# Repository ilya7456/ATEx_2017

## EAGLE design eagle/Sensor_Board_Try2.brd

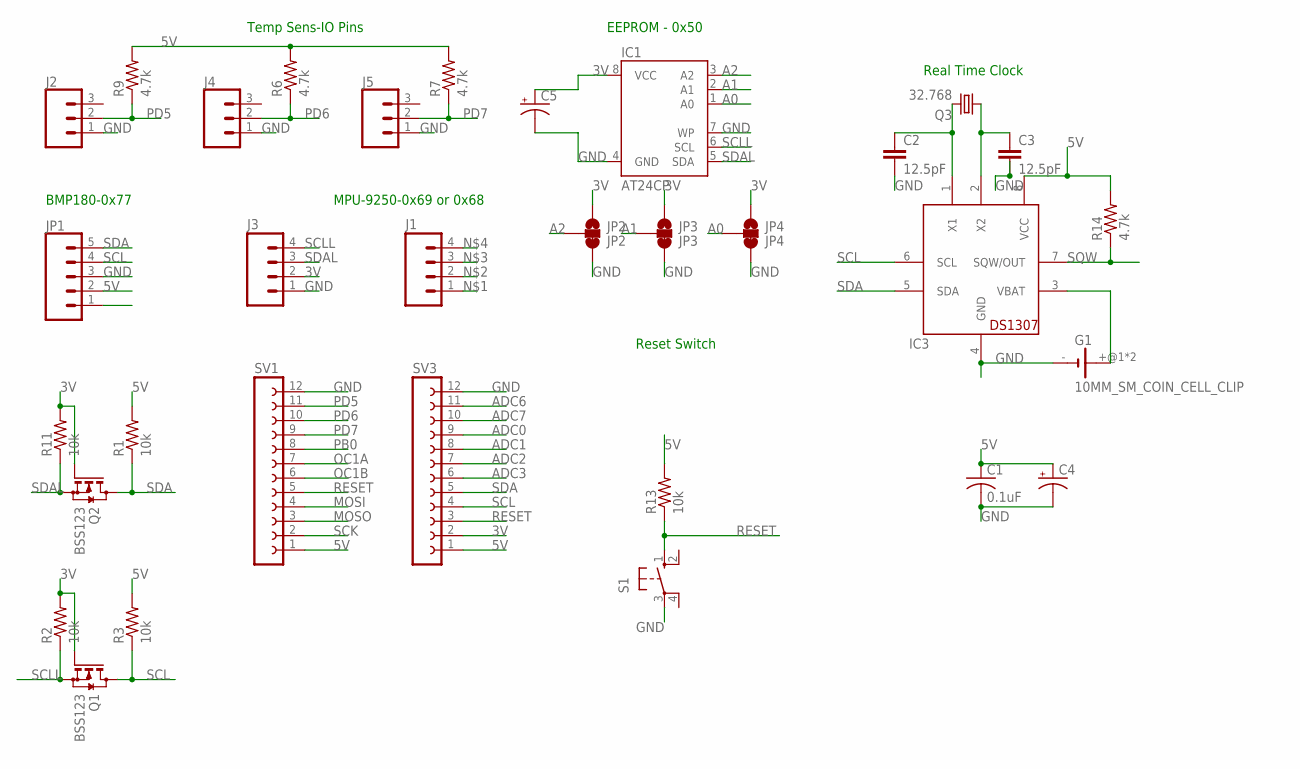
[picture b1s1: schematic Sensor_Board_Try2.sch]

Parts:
C1: 0.1uF; C025-025X050
C2, C3: 12.5pF; C0805
C4, C5: CPOL-USE2-4; E2-4
G1: 10MM_SM_COIN_CELL_CLIP
IC1: AT24CP; DIL08
IC3: DS1307; DIL08
J1, J3: M04PTH; 1X04
J2, J4, J5: CONN_03; 1X03
JP1: CONN_05; 1X05
JP2: JP2; SMT-JUMPER_3_1-NC_TRACE_SILK
JP3: JP3; SMT-JUMPER_3_1-NC_TRACE_SILK
JP4: JP4; SMT-JUMPER_3_1-NC_TRACE_SILK
Q1, Q2: BSS123; SOT23
Q3: 32.768; TC38H
R1, R2, R3, R11, R13: 10k; M0805
R6, R7, R9, R14: 4.7k; M0805
S1: 10-XX; B3F-10XX
SV1, SV3: FE12-1; FE12

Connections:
3V: C5.+, IC1.8 (VCC), J3.2, JP2.1, JP3.1, JP4.1, Q1.1 (G), Q2.1 (G), R2.2, R11.2, SV3.2
5V: C1.1, C4.+, IC3.8 (VCC), JP1.2, R1.2, R3.2, R6.2, R7.2, R9.2, R13.2, R14.2, SV1.1, SV3.1
A0: IC1.1 (A0), JP4.2
A1: IC1.2 (A1), JP3.2
A2: IC1.3 (A2), JP2.2
ADC0: SV3.9
ADC1: SV3.8
ADC2: SV3.7
ADC3: SV3.6
ADC6: SV3.11
ADC7: SV3.10
GND: C1.2, C2.2, C3.2, C4.-, C5.-, G1.-, IC1.4 (GND), IC1.7 (WP), IC3.4 (GND), J2.1, J3.1, J4.1, J5.1, JP1.3, JP2.3, JP3.3, JP4.3, S1.3, SV1.12, SV3.12
MOSI: SV1.4
MOSO: SV1.3
unnamed: C2.1, IC3.1 (X1), Q3.2
unnamed: C3.1, IC3.2 (X2), Q3.1
OC1A: SV1.7
OC1B: SV1.6
PB0: SV1.8
PD5: J2.2, R9.1, SV1.11
PD6: J4.2, R6.1, SV1.10
PD7: J5.2, R7.1, SV1.9
RESET: R13.1, S1.1 (S), SV1.5, SV3.3
SCK: SV1.2
SCL: IC3.6 (SCL), JP1.4, Q1.3 (D), R3.1, SV3.4
SCLL: IC1.6 (SCL), J3.4, Q1.2 (S), R2.1
SDA: IC3.5 (SDA), JP1.5, Q2.3 (D), R1.1, SV3.5
SDAL: IC1.5 (SDA), J3.3, Q2.2 (S), R11.1
SQW: IC3.7 (SQW/OUT), R14.1
VBAT: G1.+@1 (+), G1.+@2 (+), IC3.3 (VBAT)

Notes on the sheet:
BMP180-0x77
MPU-9250-0x69 or 0x68
Temp Sens-IO Pins
EEPROM - 0x50
Reset Switch
Real Time Clock

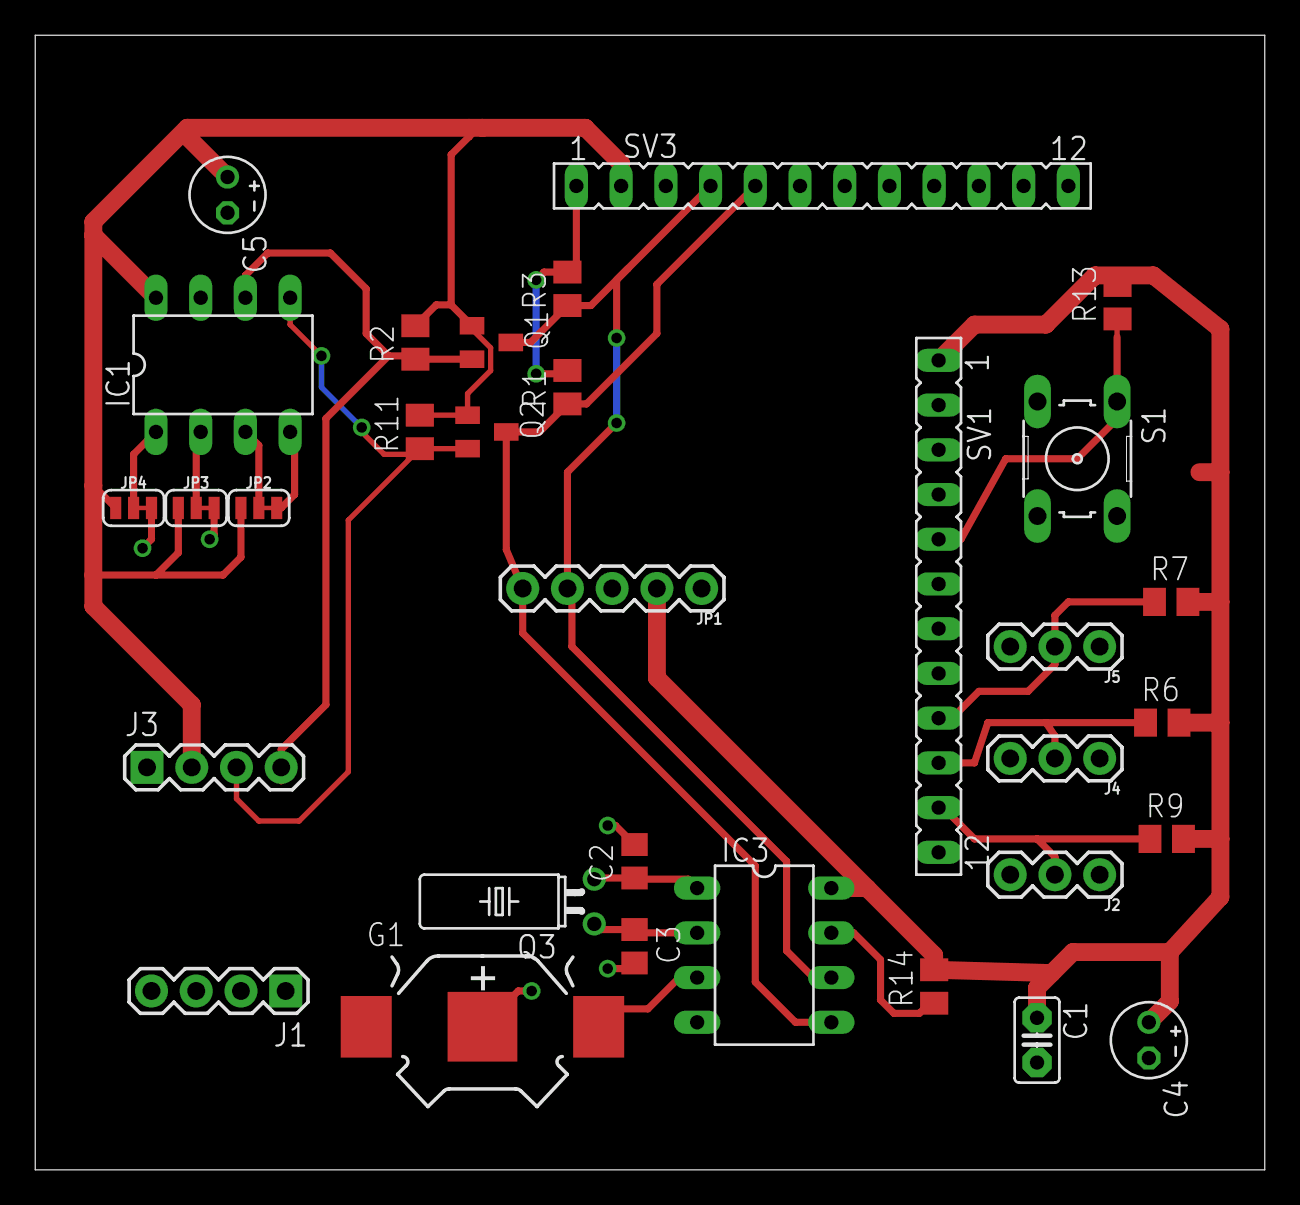
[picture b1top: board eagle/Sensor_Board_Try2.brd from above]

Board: 2 copper layers, 69.8 x 64.4 mm, 32 parts (0 on the bottom side), 18 nets.

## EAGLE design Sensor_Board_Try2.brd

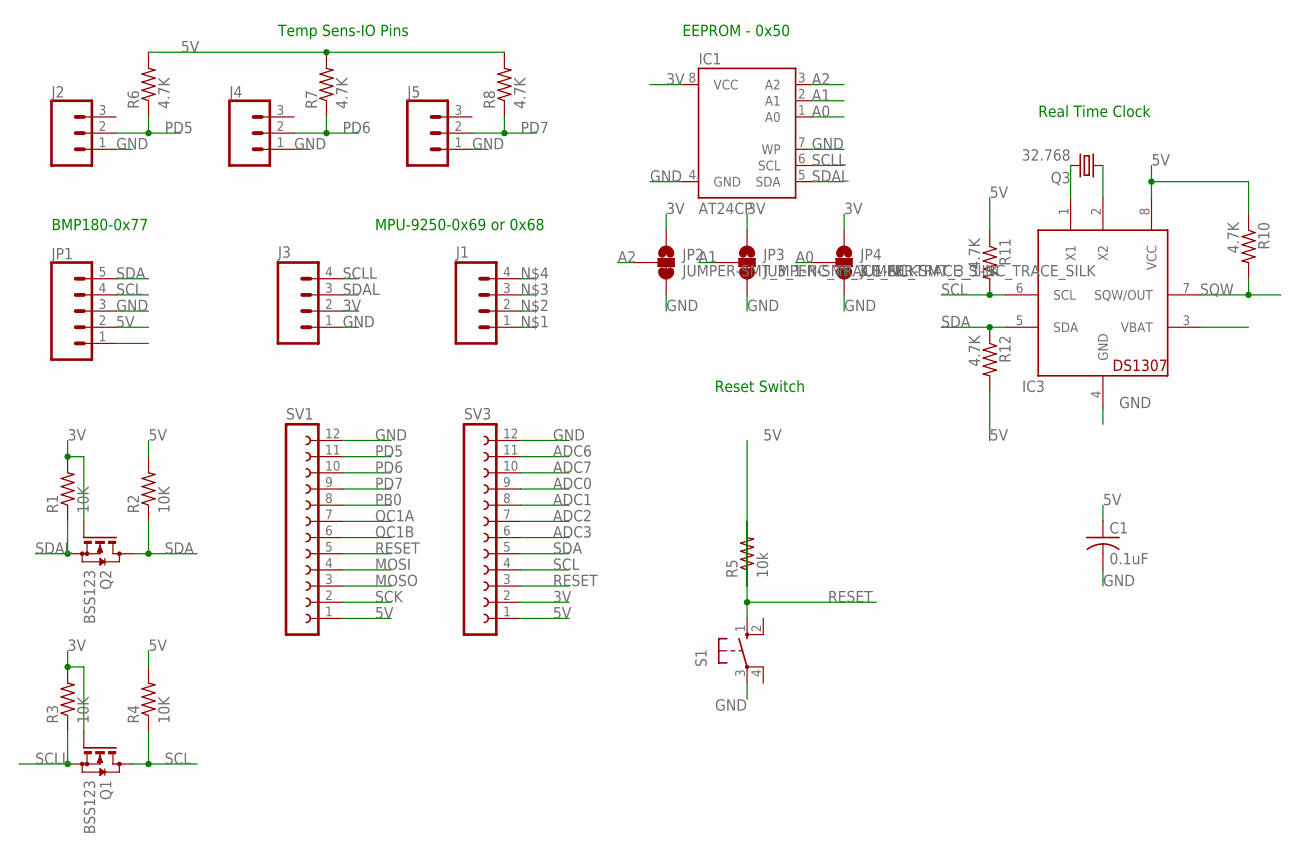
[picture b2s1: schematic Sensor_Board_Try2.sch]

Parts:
C1: 0.1uF; C025-025X050
IC1: AT24CP; DIL08
IC3: DS1307; DIL08
J1, J3: M04PTH; 1X04
J2, J4, J5: CONN_03; 1X03
JP1: CONN_05; 1X05
JP2, JP3, JP4: JUMPER-SMT_3_1-NC_TRACE_SILK; SMT-JUMPER_3_1-NC_TRACE_SILK
Q1, Q2: BSS123; SOT23
Q3: 32.768; TC38H
R1, R2, R3, R4: 10K; M1406
R5: 10k; M1406
R6, R7, R8, R10, R11, R12: 4.7K; M1406
S1: 10-XX; B3F-10XX
SV1, SV3: FE12-1; FE12

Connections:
3V: IC1.8 (VCC), J3.2, JP2.1, JP3.1, JP4.1, Q1.1 (G), Q2.1 (G), R1.2, R3.2, SV3.2
5V: C1.1, IC3.8 (VCC), JP1.2, R2.2, R4.2, R5.1, R6.2, R7.2, R8.2, R10.1, R11.1, R12.2, SV1.1, SV3.1
A0: IC1.1 (A0), JP4.2
A1: IC1.2 (A1), JP3.2
A2: IC1.3 (A2), JP2.2
ADC0: SV3.9
ADC1: SV3.8
ADC2: SV3.7
ADC3: SV3.6
ADC6: SV3.11
ADC7: SV3.10
GND: C1.2, IC1.4 (GND), IC1.7 (WP), IC3.4 (GND), J2.1, J3.1, J4.1, J5.1, JP1.3, JP2.3, JP3.3, JP4.3, S1.3, SV1.12, SV3.12
MOSI: SV1.4
MOSO: SV1.3
unnamed: IC3.1 (X1), Q3.2
unnamed: IC3.2 (X2), Q3.1
OC1A: SV1.7
OC1B: SV1.6
PB0: SV1.8
PD5: J2.2, R6.1, SV1.11
PD6: J4.2, R7.1, SV1.10
PD7: J5.2, R8.1, SV1.9
RESET: R5.2, S1.1 (S), SV1.5, SV3.3
SCK: SV1.2
SCL: IC3.6 (SCL), JP1.4, Q1.3 (D), R4.1, R11.2, SV3.4
SCLL: IC1.6 (SCL), J3.4, Q1.2 (S), R3.1
SDA: IC3.5 (SDA), JP1.5, Q2.3 (D), R2.1, R12.1, SV3.5
SDAL: IC1.5 (SDA), J3.3, Q2.2 (S), R1.1
SQW: IC3.7 (SQW/OUT), R10.2

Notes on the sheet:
BMP180-0x77
MPU-9250-0x69 or 0x68
Temp Sens-IO Pins
EEPROM - 0x50
Reset Switch
Real Time Clock

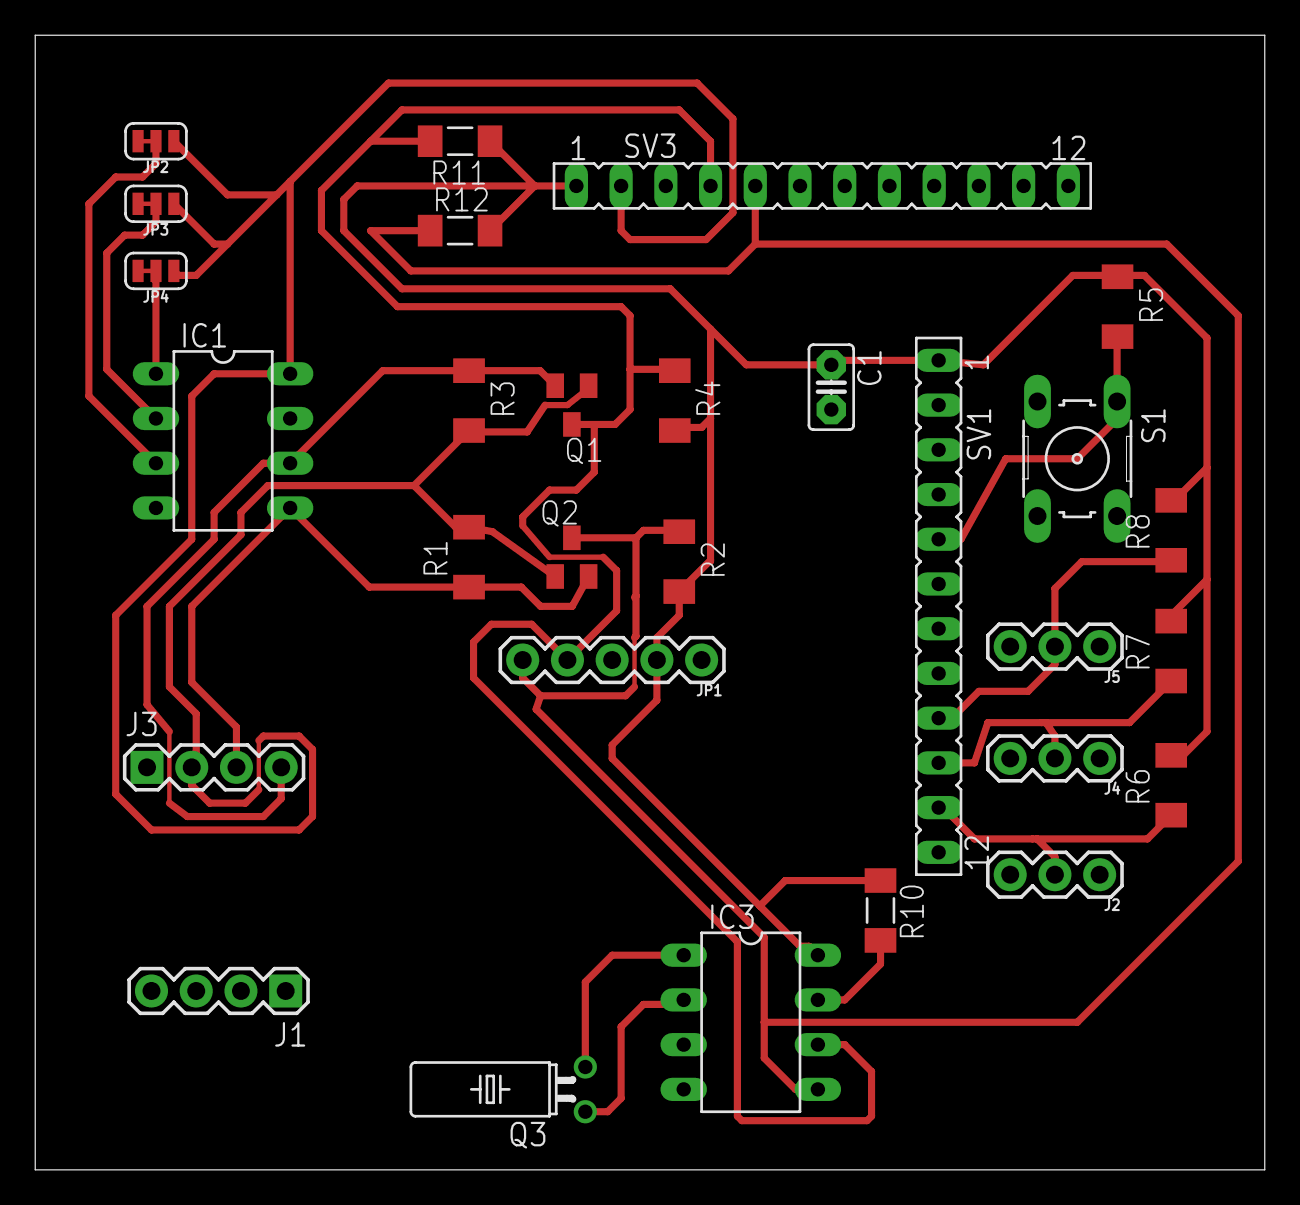
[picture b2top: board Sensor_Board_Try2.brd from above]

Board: 2 copper layers, 69.8 x 64.4 mm, 29 parts (0 on the bottom side), 17 nets.

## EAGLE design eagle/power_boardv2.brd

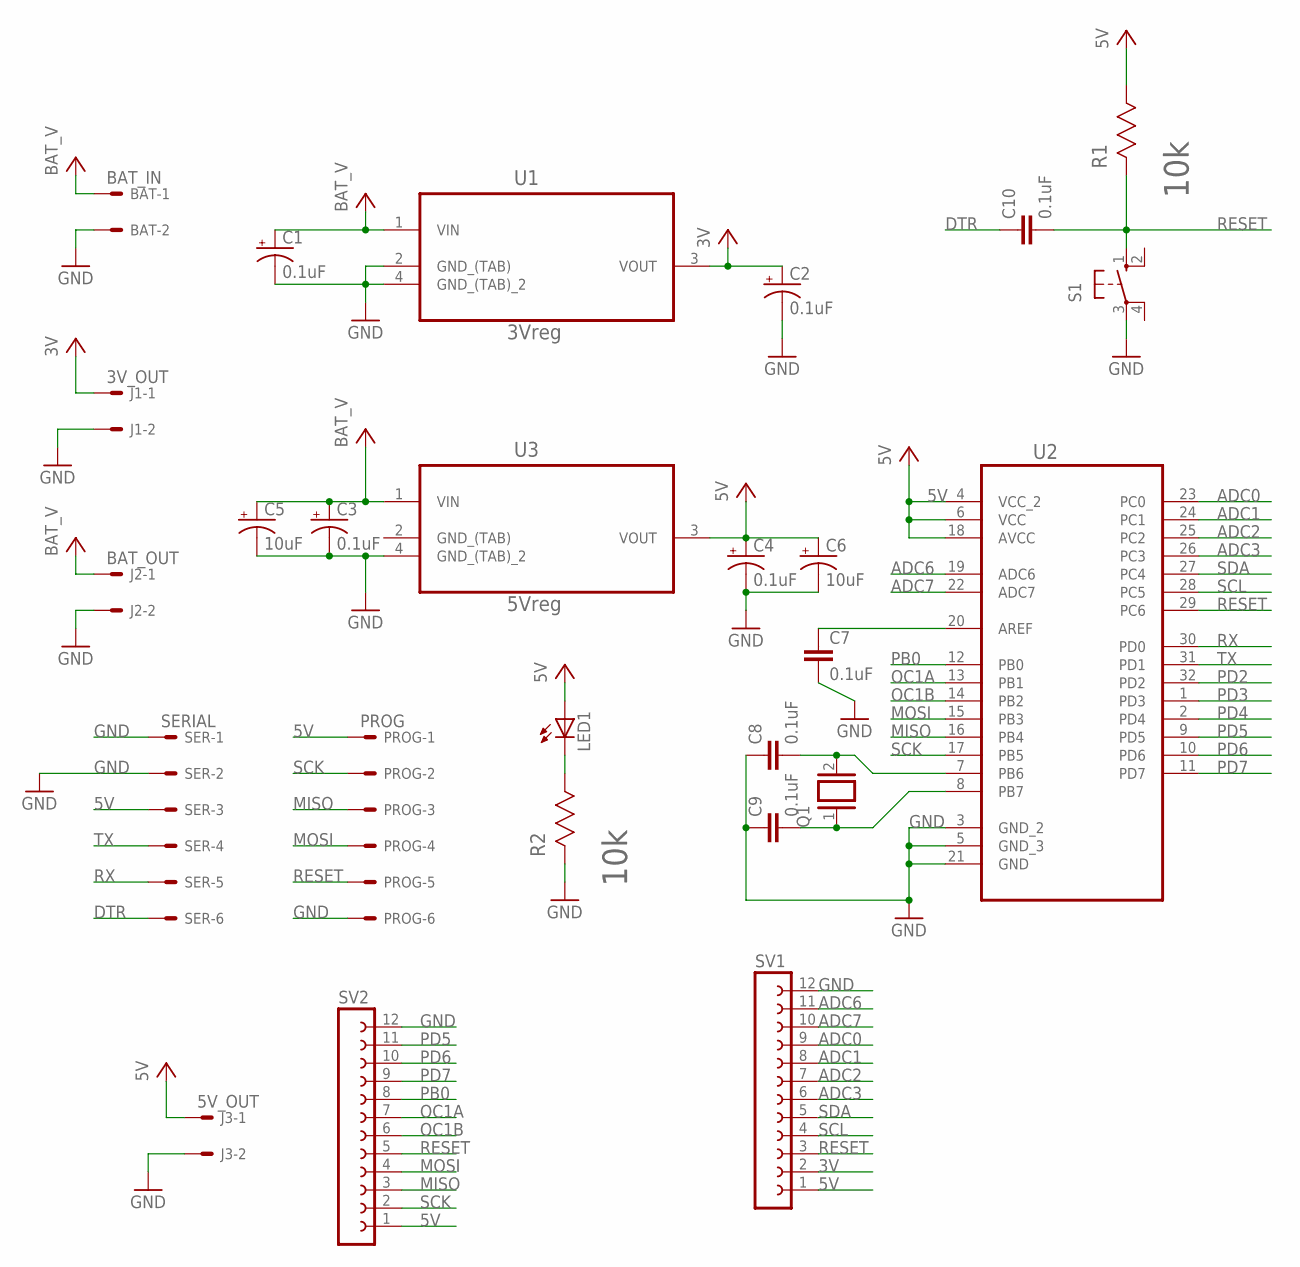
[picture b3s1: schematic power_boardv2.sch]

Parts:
BAT: BAT_IN; 7395-02
C1, C2, C3, C4: 0.1uF; E2,5-5
C5, C6: 10uF; E2,5-5
C7, C8, C9, C10: 0.1uF; C2.5-3
J1: 3V_OUT; 7395-02
J2: BAT_OUT; 7395-02
J3: 5V_OUT; 7395-02
LED1: LED_E; LED_1206
PROG: PROG; 7395-06
Q1: XTAL/S; QS
R1, R2: 10k; RESC2013X65N
S1: 10-XX; B3F-10XX
SER: SERIAL; 7395-06
SV1, SV2: FE12-1; FE12
U1: 3Vreg; SOT230P700X180-4N
U2: ATMEGA328P-AU; QFP80P900X900X120-32N
U3: 5Vreg; SOT230P700X180-4N

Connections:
3V: C2.+, J1.1, SV1.2, U1.3 (VOUT)
5V: C4.+, C6.+, J3.1, LED1.A, PROG.1, R1.1, SER.3, SV1.1, SV2.1, U2.4 (VCC_2), U2.6 (VCC), U2.18 (AVCC), U3.3 (VOUT)
ADC0: SV1.9, U2.23 (PC0)
ADC1: SV1.8, U2.24 (PC1)
ADC2: SV1.7, U2.25 (PC2)
ADC3: SV1.6, U2.26 (PC3)
ADC6: SV1.11, U2.19 (ADC6)
ADC7: SV1.10, U2.22 (ADC7)
BAT_V: BAT.1, C1.+, C3.+, C5.+, J2.1, U1.1 (VIN), U3.1 (VIN)
DTR: C10.1, SER.6
GND: BAT.2, C1.-, C2.-, C3.-, C4.-, C5.-, C6.-, C7.2, C8.1, C9.1, J1.2, J2.2, J3.2, PROG.6, R2.2, S1.3, SER.1, SER.2, SV1.12, SV2.12, U1.2 (GND_(TAB)), U1.4 (GND_(TAB)_2), U2.3 (GND_2), U2.5 (GND_3), U2.21 (GND), U3.4 (GND_(TAB)_2)
MISO: PROG.3, SV2.3, U2.16 (PB4)
MOSI: PROG.4, SV2.4, U2.15 (PB3)
unnamed: C7.1, U2.20 (AREF)
unnamed: C8.2, Q1.2, U2.7 (PB6)
unnamed: C9.2, Q1.1, U2.8 (PB7)
unnamed: LED1.C, R2.1
OC1A: SV2.7, U2.13 (PB1)
OC1B: SV2.6, U2.14 (PB2)
PB0: SV2.8, U2.12 (PB0)
PD2: U2.32 (PD2)
PD3: U2.1 (PD3)
PD4: U2.2 (PD4)
PD5: SV2.11, U2.9 (PD5)
PD6: SV2.10, U2.10 (PD6)
PD7: SV2.9, U2.11 (PD7)
RESET: C10.2, PROG.5, R1.2, S1.1 (S), SV1.3, SV2.5, U2.29 (PC6)
RX: SER.5, U2.30 (PD0)
SCK: PROG.2, SV2.2, U2.17 (PB5)
SCL: SV1.4, U2.28 (PC5)
SDA: SV1.5, U2.27 (PC4)
TX: SER.4, U2.31 (PD1)

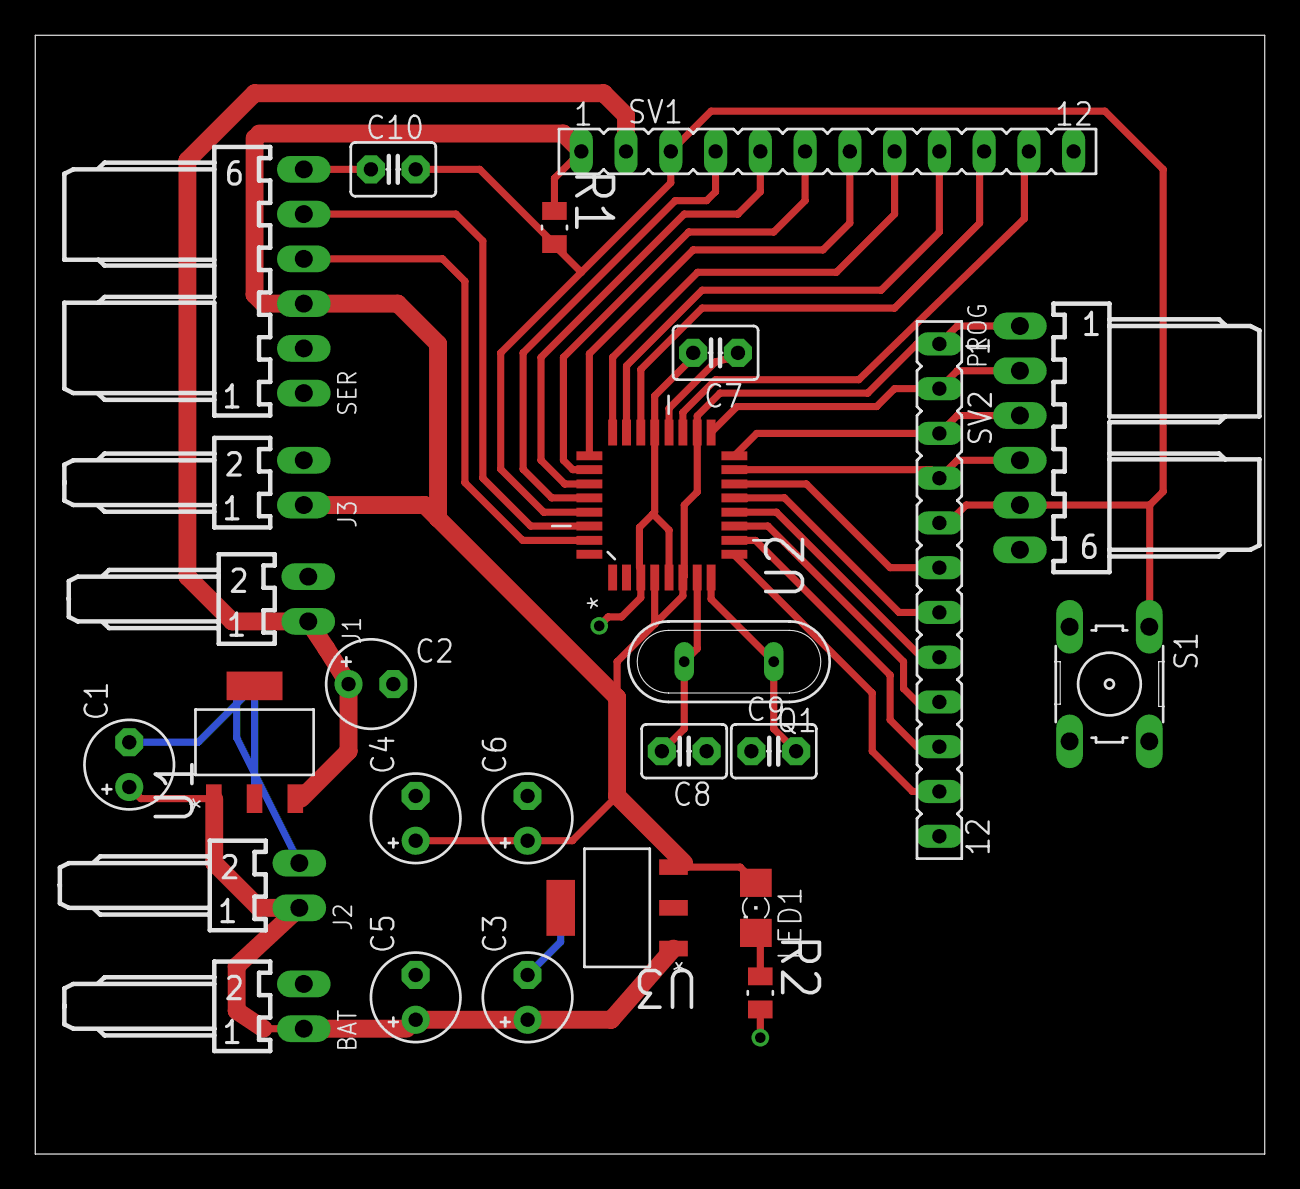
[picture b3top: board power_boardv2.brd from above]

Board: 2 copper layers, 69.8 x 63.5 mm, 26 parts (0 on the bottom side), 29 nets.

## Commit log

2017-02-05 init
    first commit
2017-02-05 test0
    test
2017-02-05 libraries
    libraries
2017-02-06 TempSensor
2017-02-19 BMP180 Pressure Sensor
2017-03-09 Add files via upload
    This is the eeprom code. I just need to change it over to i2c dev for reading and writing byte to eeprom. Working on eagle.
2017-03-12 added schematic and board files to eagle folder
2017-03-21 Sensor PCB
    Sensor PCB
2017-03-26 Add files via upload
    This is my second try on the board. I had trouble getting the SCL wire routed and I came of the best solution I could at the moment. Another issue is board errors on the jumpers. I do not know why th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
2017-03-27 took out some of the serial prints
    serial update
2017-04-05 few changes to the board
2017-04-06 final version of the boards
2017-04-06 moved the boards into eagle folder
2017-04-28 Add files via upload
    These two files reset the EEPROM and run the Finite state machine. The other Temperature pin needs to be set in order to get the second sensor to work.
2017-04-28 Pins need to be changed in FSM to add the other temp sensors
2017-04-28 Final Code
    One thing to do is adding the right pin, time and testing for the ISR for cutdown.
2017-04-28 ISR is in here. Flight ready
2017-04-28 ISR is in here

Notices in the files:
parts and their libraries:
SparkFun-Connectors: Licensing: Creative Commons ShareAlike 4.0 International - https://creativecommons.org/licenses/by-sa/4.0
